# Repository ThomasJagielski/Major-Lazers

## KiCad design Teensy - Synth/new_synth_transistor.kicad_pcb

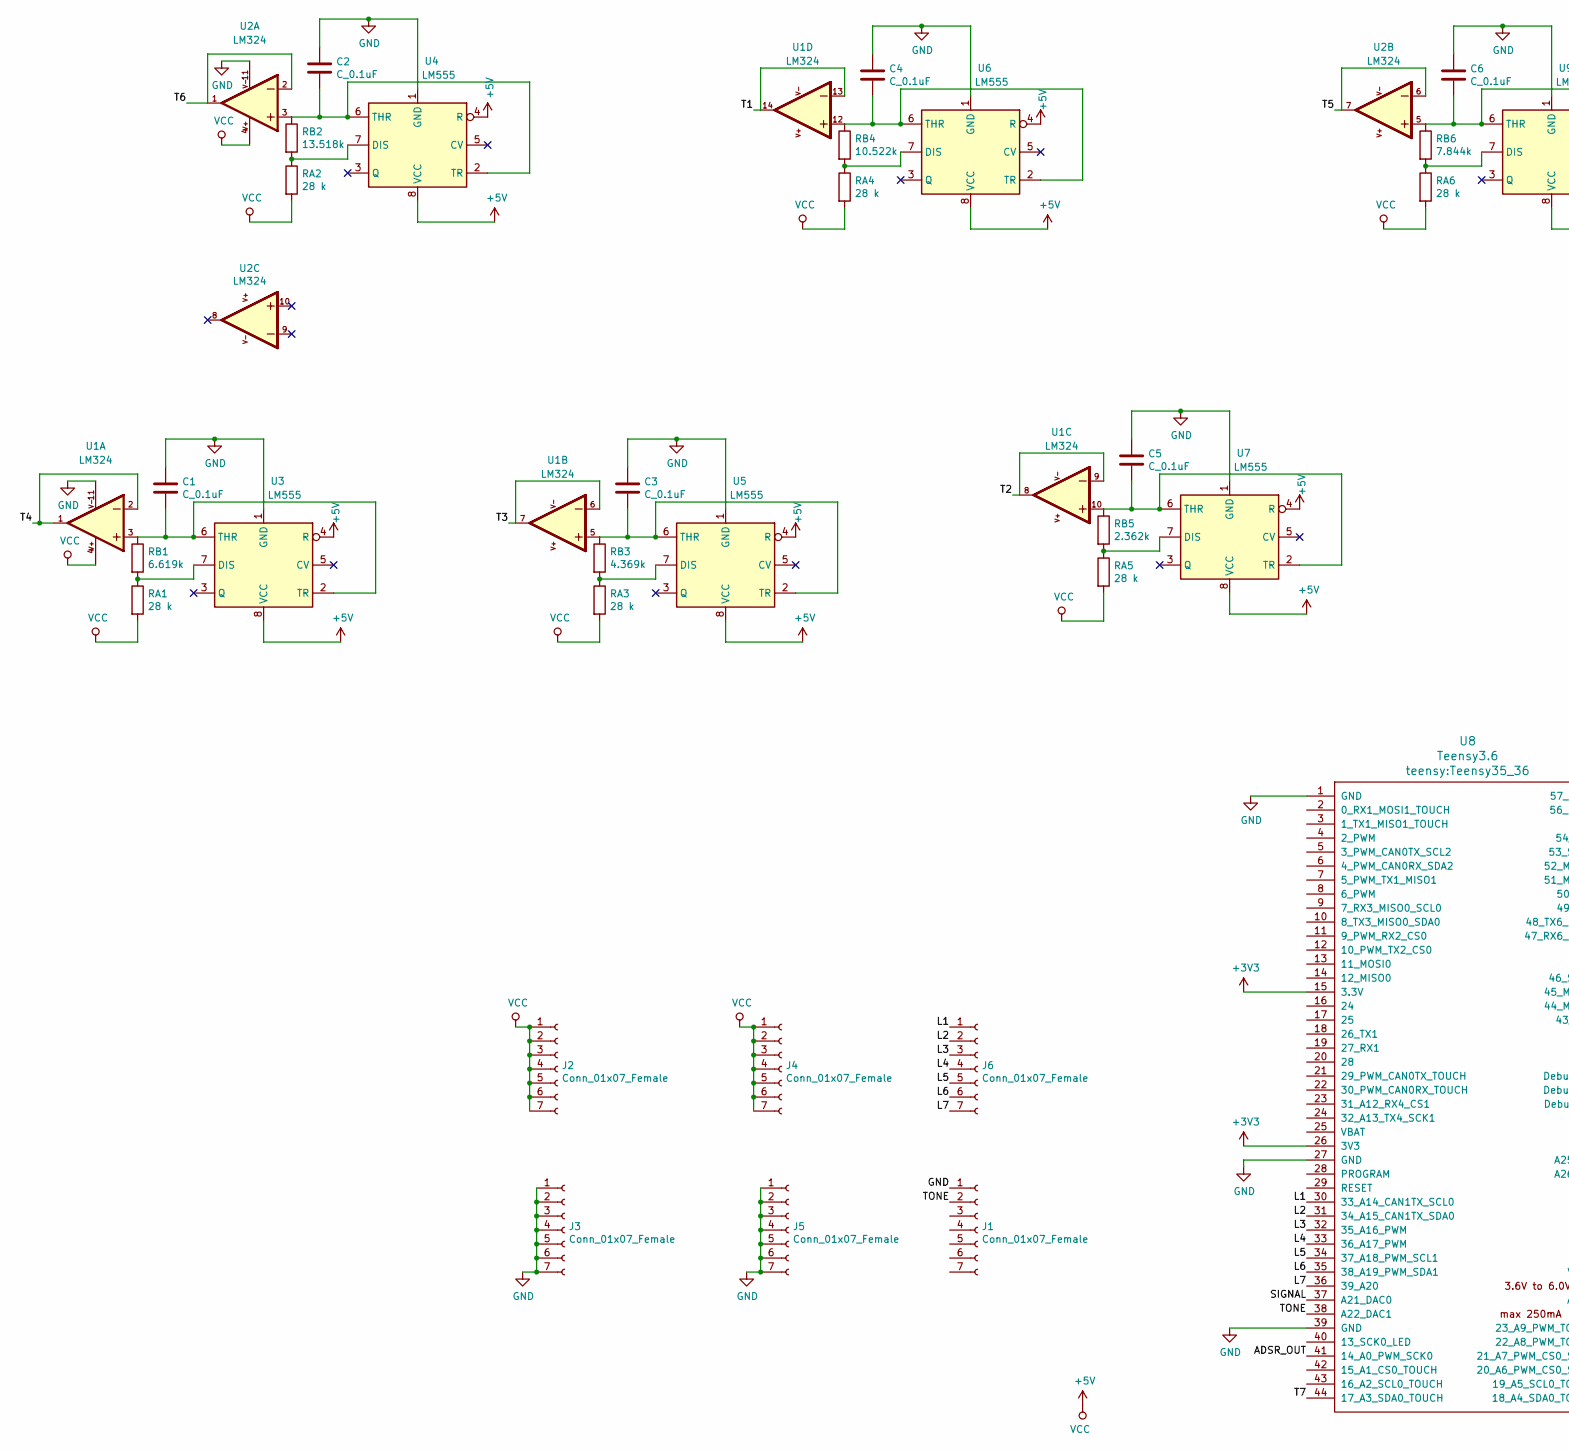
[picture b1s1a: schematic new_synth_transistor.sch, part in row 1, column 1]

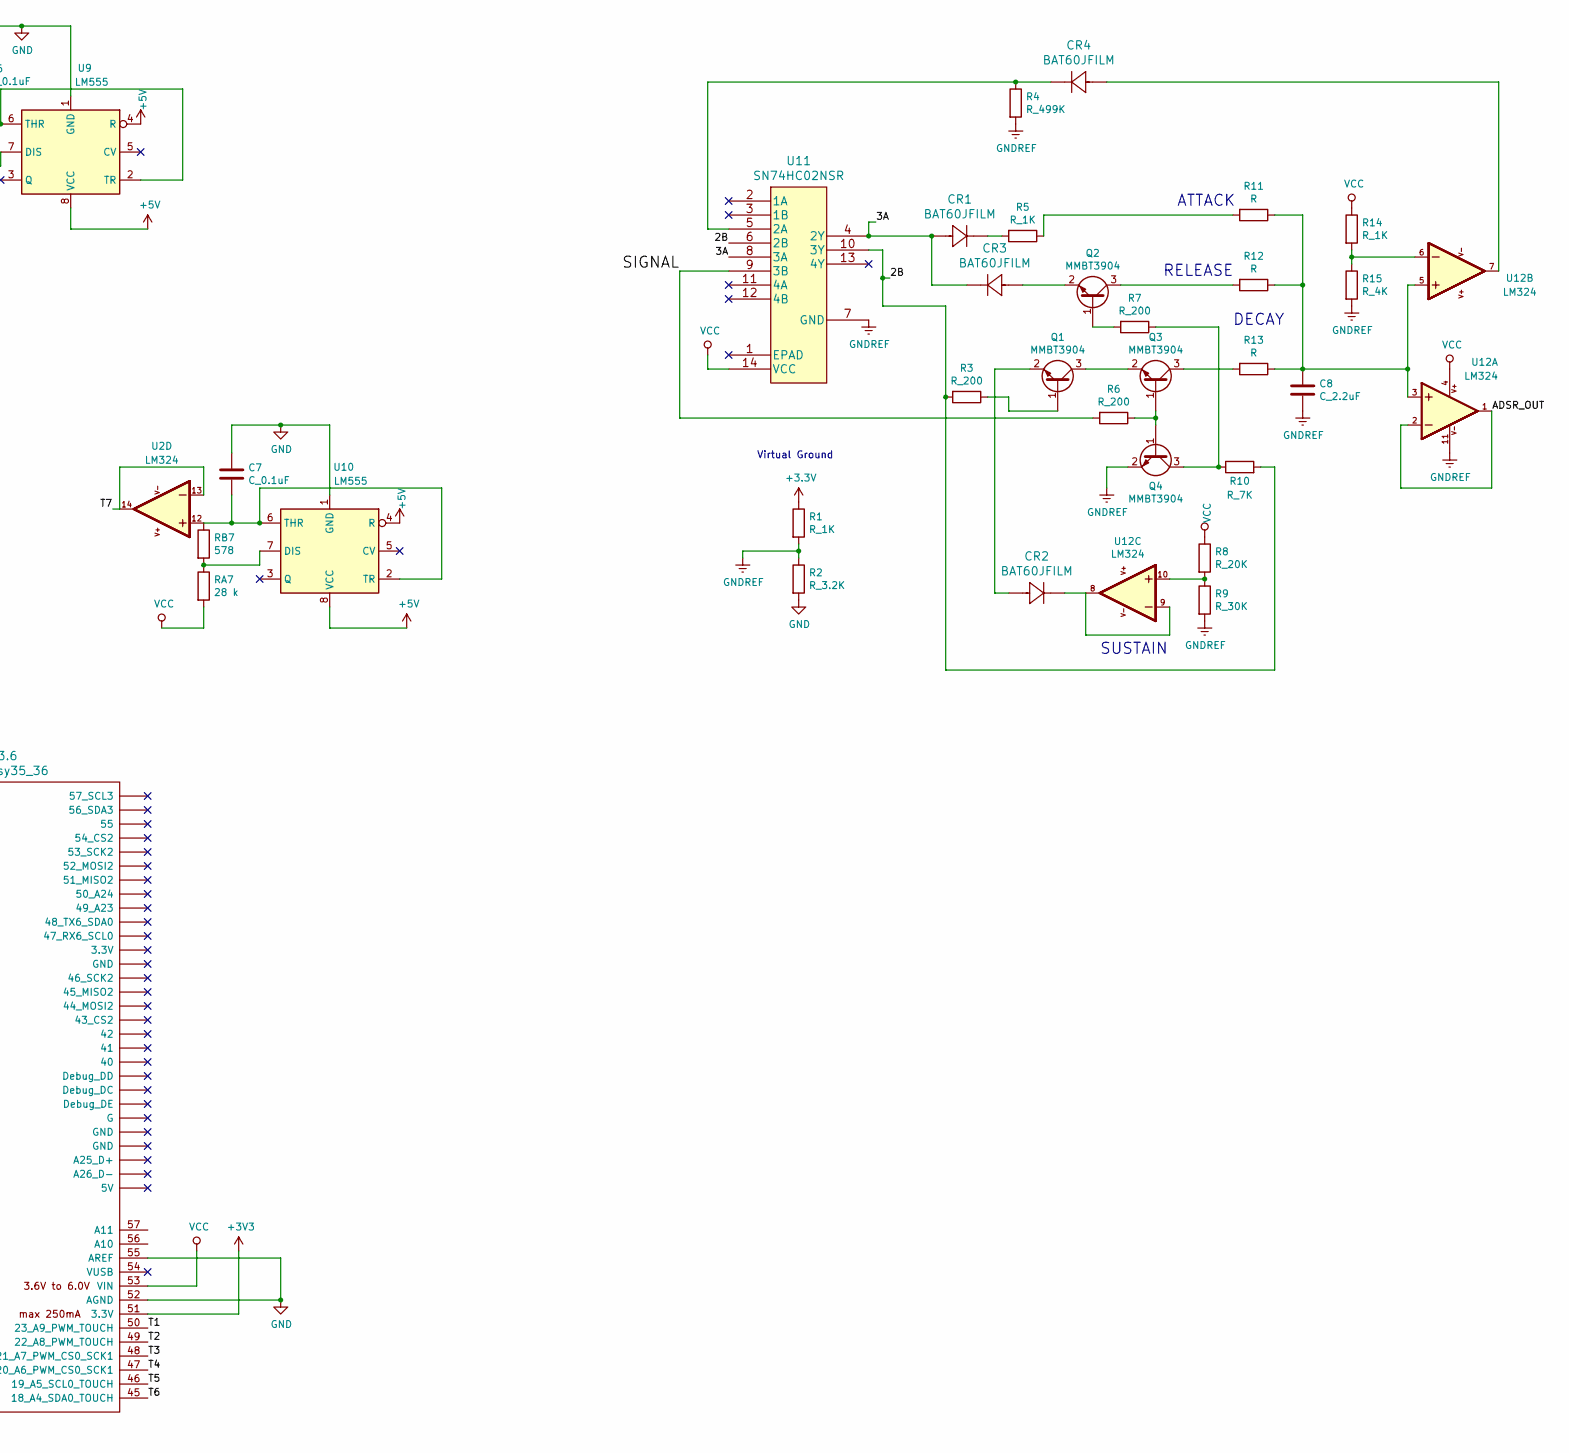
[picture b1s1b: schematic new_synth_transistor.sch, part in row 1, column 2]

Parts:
C1, C2, C3, C4, C5, C6, C7: C_0.1uF; C_0805_2012Metric
C8: C_2.2uF; C_0805_2012Metric
CR1, CR2, CR3, CR4: BAT60JFILM
J1, J2, J3, J4, J5, J6: Conn_01x07_Female; PinHeader_1x07_P2.54mm_Vertical
Q1, Q2, Q3, Q4: MMBT3904; SOT-23
R1, R5, R14: R_1K; R_0805_2012Metric
R2: R_3.2K; R_0805_2012Metric
R3, R6, R7: R_200; R_0805_2012Metric
R4: R_499K; R_0805_2012Metric
R8: R_20K; R_0805_2012Metric
R9: R_30K; R_0805_2012Metric
R10: R_7K; R_0805_2012Metric
R11, R12, R13: R; R_0805_2012Metric
R15: R_4K; R_0805_2012Metric
RA1, RA2, RA3, RA4, RA5, RA6, RA7: 28 k; R_0805_2012Metric
RB1: 6.619k; R_0805_2012Metric
RB2: 13.518k; R_0805_2012Metric
RB3: 4.369k; R_0805_2012Metric
RB4: 10.522k; R_0805_2012Metric
RB5: 2.362k; R_0805_2012Metric
RB6: 7.844k; R_0805_2012Metric
RB7: 578; R_0805_2012Metric
U1, U2, U12: LM324; SOIC127P600X175-14N
U3, U4, U5, U6, U7, U9, U10: LM555; SO08
U8: Teensy3.6; Teensy35_36
U11: SN74HC02NSR

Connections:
+5V: J2.1, J2.2, J2.3, J2.4, J2.5, J2.6, J2.7, J4.1, J4.2, J4.3, J4.4, J4.5, J4.6, J4.7, R8.1, R14.1, RA1.2, RA2.2, RA3.2, RA4.2, RA5.2, RA6.2, RA7.2, U1.4 (VCC+), U2.4 (VCC+), U3.4 (R), U3.8 (VCC), U4.4 (R), U4.8 (VCC), U5.4 (R), U5.8 (VCC), U6.4 (R), U6.8 (VCC), U7.4 (R), U7.8 (VCC), U8.53 (VIN), U9.4 (R), U9.8 (VCC), U10.4 (R), U10.8 (VCC), U11.14 (VCC), U12.4 (VCC+)
/2B: R3.2, R10.2, U11.6 (2B), U11.10 (3Y)
/3A: CR1.2, CR3.1, U11.4 (2Y), U11.8 (3A)
/ADSR_OUT: U8.41 (14_A0_PWM_SCK0), U12.1 (OUTPUT1), U12.2 (INVERTING_INPUT1)
/L1: J6.1, U8.30 (33_A14_CAN1TX_SCL0)
/L2: J6.2, U8.31 (34_A15_CAN1TX_SDA0)
/L3: J6.3, U8.32 (35_A16_PWM)
/L4: J6.4, U8.33 (36_A17_PWM)
/L5: J6.5, U8.34 (37_A18_PWM_SCL1)
/L6: J6.6, U8.35 (38_A19_PWM_SDA1)
/L7: J6.7, U8.36 (39_A20)
/SIGNAL: R6.2, U8.37 (A21_DAC0), U11.9 (3B)
/T1: U1.13 (INVERTING_INPUT4), U1.14 (OUTPUT4), U8.50 (23_A9_PWM_TOUCH)
/T2: U1.8 (OUTPUT3), U1.9 (INVERTING_INPUT3), U8.49 (22_A8_PWM_TOUCH)
/T3: U1.6 (INVERTING_INPUT2), U1.7 (OUTPUT2), U8.48 (21_A7_PWM_CS0_SCK1)
/T4: U1.1 (OUTPUT1), U1.2 (INVERTING_INPUT1), U8.47 (20_A6_PWM_CS0_SCK1)
/T5: U2.6 (INVERTING_INPUT2), U2.7 (OUTPUT2), U8.46 (19_A5_SCL0_TOUCH)
/T6: U2.1 (OUTPUT1), U2.2 (INVERTING_INPUT1), U8.45 (18_A4_SDA0_TOUCH)
/T7: U2.13 (INVERTING_INPUT4), U2.14 (OUTPUT4), U8.44 (17_A3_SDA0_TOUCH)
/TONE: J1.2, U8.38 (A22_DAC1)
GND: C1.1, C2.1, C3.1, C4.1, C5.1, C6.1, C7.1, J1.1, J3.1, J3.2, J3.3, J3.4, J3.5, J3.6, J3.7, J5.1, J5.2, J5.3, J5.4, J5.5, J5.6, J5.7, R2.2, U1.11 (VCC-), U2.11 (VCC-), U3.1 (GND), U4.1 (GND), U5.1 (GND), U6.1 (GND), U7.1 (GND), U8.1 (GND), U8.27 (GND), U8.39 (GND), U8.52 (AGND), U8.55 (AREF), U9.1 (GND), U10.1 (GND)
GNDREF: C8.2, Q4.2 (E), R1.2, R2.1, R4.2, R9.2, R15.2, U11.7 (GND), U12.11 (VCC-)
unnamed: C1.2, RB1.1, U1.3 (NON-INVERTING_INPUT1), U3.2 (TR), U3.6 (THR)
unnamed: C2.2, RB2.1, U2.3 (NON-INVERTING_INPUT1), U4.2 (TR), U4.6 (THR)
unnamed: C3.2, RB3.1, U1.5 (NON-INVERTING_INPUT2), U5.2 (TR), U5.6 (THR)
unnamed: C4.2, RB4.1, U1.12 (NON-INVERTING_INPUT4), U6.2 (TR), U6.6 (THR)
unnamed: C5.2, RB5.1, U1.10 (NON-INVERTING_INPUT3), U7.2 (TR), U7.6 (THR)
unnamed: C6.2, RB6.1, U2.5 (NON-INVERTING_INPUT2), U9.2 (TR), U9.6 (THR)
unnamed: C7.2, RB7.1, U2.12 (NON-INVERTING_INPUT4), U10.2 (TR), U10.6 (THR)
unnamed: C8.1, R11.1, R12.1, R13.1, U12.3 (NON-INVERTING_INPUT1), U12.5 (NON-INVERTING_INPUT2)
unnamed: CR1.1, R5.2
unnamed: CR2.1, U12.8 (OUTPUT3), U12.9 (INVERTING_INPUT3)
unnamed: CR2.2, Q1.2 (E)
unnamed: CR3.2, Q2.2 (E)
unnamed: CR4.1, R4.1, U11.5 (2A)
unnamed: CR4.2, U12.7 (OUTPUT2)
unnamed: Q1.1 (B), R3.1
unnamed: Q1.3 (C), Q3.2 (E)
unnamed: Q2.1 (B), R7.2
unnamed: Q2.3 (C), R12.2
unnamed: Q3.1 (B), Q4.1 (B), R6.1
unnamed: Q3.3 (C), R13.2
unnamed: Q4.3 (C), R7.1, R10.1
unnamed: R8.2, R9.1, U12.10 (NON-INVERTING_INPUT3)
unnamed: R5.1, R11.2
unnamed: R14.2, R15.1, U12.6 (INVERTING_INPUT2)
unnamed: RA1.1, RB1.2, U3.7 (DIS)
unnamed: RA2.1, RB2.2, U4.7 (DIS)
unnamed: RA3.1, RB3.2, U5.7 (DIS)
unnamed: RA4.1, RB4.2, U6.7 (DIS)
unnamed: RA5.1, RB5.2, U7.7 (DIS)
unnamed: RA6.1, RB6.2, U9.7 (DIS)
unnamed: RA7.1, RB7.2, U10.7 (DIS)

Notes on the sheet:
SUSTAIN
DECAY
ATTACK
RELEASE
Virtual Ground

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
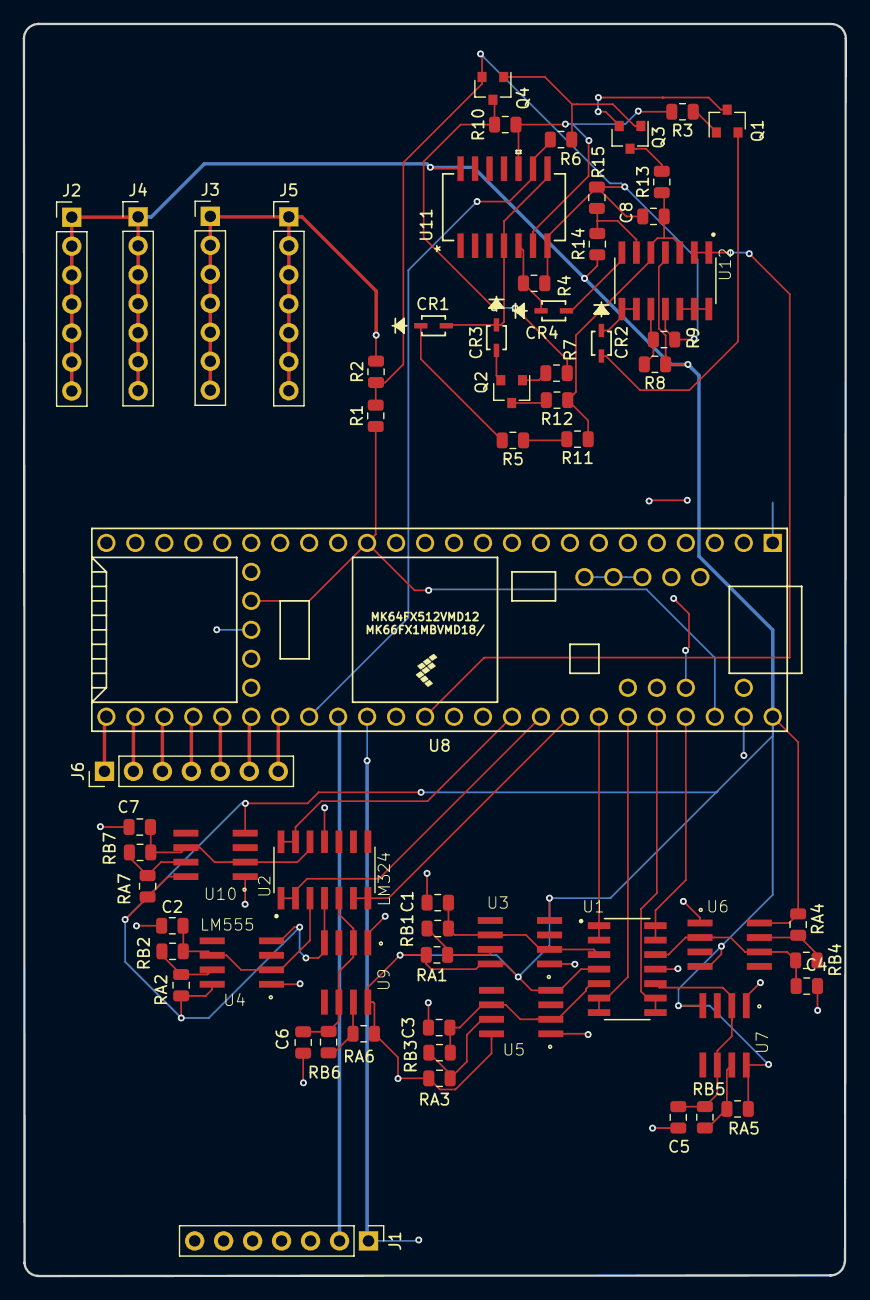
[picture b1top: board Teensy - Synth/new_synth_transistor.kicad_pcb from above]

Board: 2 copper layers, 72.1 x 109.8 mm, 63 parts (0 on the bottom side), 54 nets.

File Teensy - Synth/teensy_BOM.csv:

"Id";"Designator";"Package";"Quantity";"Designation";"Supplier and ref";
1;"U12,U1,U2";"SOIC127P600X175-14N";3;"LM324";;;
2;"U10,U6,U4,U3,U5,U7,U9";"SO08";7;"LM555";;;
3;"U11";"SN74HC02NSR";1;"SN74HC02NSR";;;
4;"U8";"Teensy35_36";1;"Teensy3.6";;;
5;"C1,C2,C3,C4,C5,C6,C7";"C_0805_2012Metric";7;"C_0.1uF";;;
6;"C8";"C_0805_2012Metric";1;"C_2.2uF";;;
7;"CR1,CR2,CR3,CR4";"BAT60JFILM";4;"BAT60JFILM";;;
8;"J1,J2,J3,J4,J5,J6";"PinHeader_1x07_P2.54mm_Vertical";6;"Conn_01x07_Female";;;
9;"Q1,Q2,Q3,Q4";"SOT-23";4;"MMBT3904";;;
10;"R1,R5,R14";"R_0805_2012Metric";3;"R_1K";;;
11;"R2";"R_0805_2012Metric";1;"R_3.2K";;;
12;"R3,R6,R7";"R_0805_2012Metric";3;"R_200";;;
13;"R4";"R_0805_2012Metric";1;"R_499K";;;
14;"R8";"R_0805_2012Metric";1;"R_20K";;;
15;"R9";"R_0805_2012Metric";1;"R_30K";;;
16;"R10";"R_0805_2012Metric";1;"R_7K";;;
17;"R11,R12,R13";"R_0805_2012Metric";3;"R";;;
18;"R15";"R_0805_2012Metric";1;"R_4K";;;
19;"RA1,RA2,RA3,RA4,RA5,RA6,RA7";"R_0805_2012Metric";7;"28 k";;;
20;"RB1";"R_0805_2012Metric";1;"6.619k";;;
21;"RB2";"R_0805_2012Metric";1;"13.518k";;;
22;"RB3";"R_0805_2012Metric";1;"4.369k";;;
23;"RB4";"R_0805_2012Metric";1;"10.522k";;;
24;"RB5";"R_0805_2012Metric";1;"2.362k";;;
25;"RB6";"R_0805_2012Metric";1;"7.844k";;;
26;"RB7";"R_0805_2012Metric";1;"578";;;

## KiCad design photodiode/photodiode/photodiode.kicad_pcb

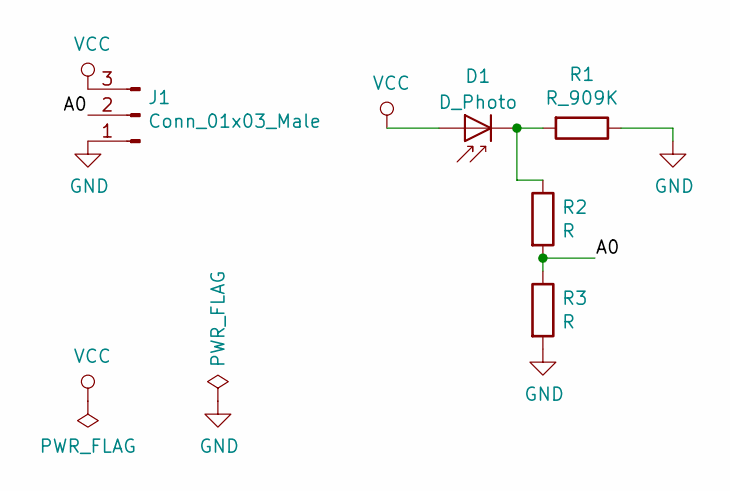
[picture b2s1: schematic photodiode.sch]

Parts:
D1: D_Photo; PinHeader_1x02_P2.54mm_Vertical
J1: Conn_01x03_Male; PinHeader_1x03_P2.54mm_Vertical
R1: R_909K; R_0805_2012Metric
R2, R3: R; R_0805_2012Metric

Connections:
/A0: J1.2, R2.2, R3.1
GND: J1.1, R1.1, R3.2
unnamed: D1.1 (K), R1.2, R2.1
VCC: D1.2 (A), J1.3

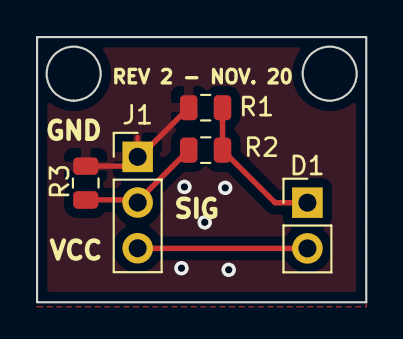
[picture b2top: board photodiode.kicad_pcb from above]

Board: 2 copper layers, 18.3 x 14.7 mm, 5 parts (0 on the bottom side), 4 nets.

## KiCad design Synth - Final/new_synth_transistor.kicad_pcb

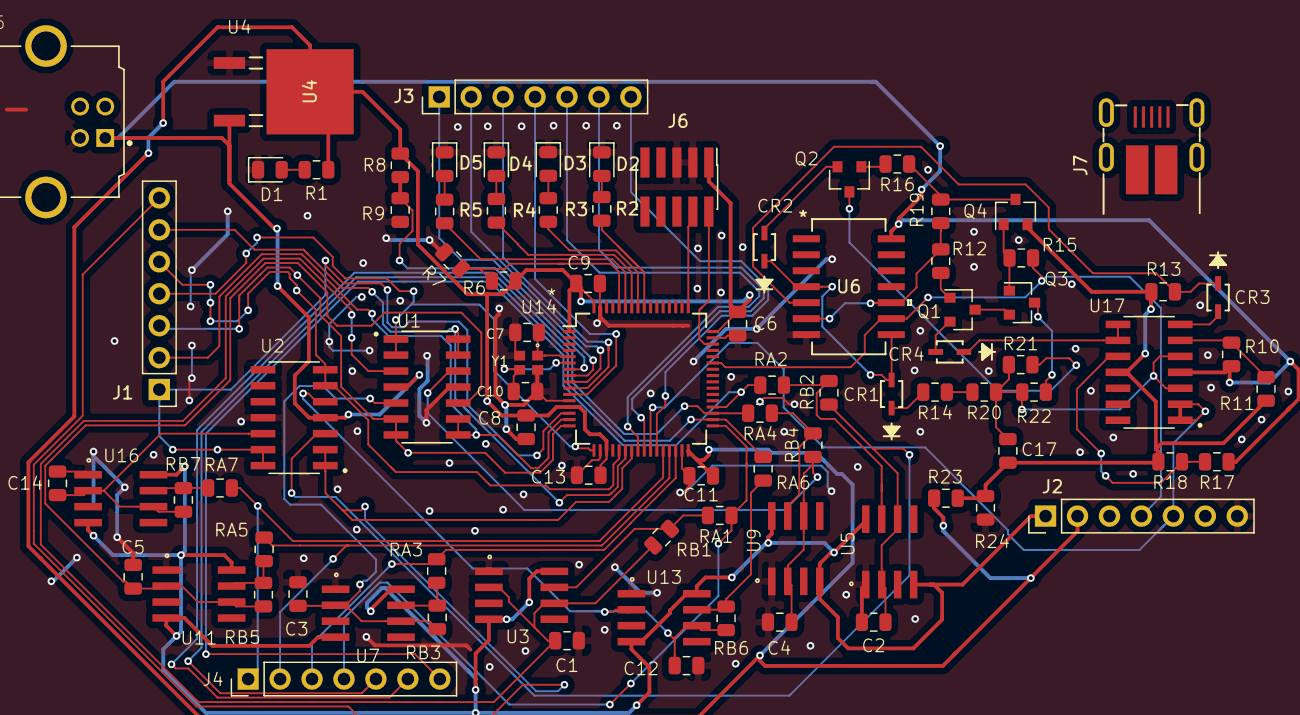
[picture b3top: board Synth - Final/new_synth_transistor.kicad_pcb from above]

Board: 2 copper layers, 87 parts (0 on the bottom side), 76 nets.

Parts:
C1, C2, C3, C4, C5, C6, C8, C9, C11, C12, C13, C14: C_0.1uF; C_0805_2012Metric
C7, C10: C_22pF; C_0805_2012Metric
C17: C_2.2uF; C_0805_2012Metric
CR1, CR2, CR3, CR4: BAT60JFILM
D1, D2, D3, D4, D5: LED; D_0805_2012Metric
J1, J2, J3, J4: Conn_01x07_Male; PinHeader_1x07_P2.54mm_Vertical
J5: USB_B; ASSMANN_AU-Y1007
J6: Conn_ARM_JTAG_SWD_10; PinHeader_2x05_P1.27mm_Vertical_SMD
J7: UJ2-MIBH-4-SMT-TR; USB_Micro_B_Male_UJ2-MIBH-4-SMT-TR
Q1, Q2, Q3, Q4: MMBT3904; SOT-23
R1, R2, R3, R4, R5, R12, R15, R16: R_200; R_0805_2012Metric
R6, R7, R8, R9: R_0; R_0805_2012Metric
R10, R14, R23: R_1K; R_0805_2012Metric
R11: R_4K; R_0805_2012Metric
R13: R_499K; R_0805_2012Metric
R17: R_20K; R_0805_2012Metric
R18: R_30K; R_0805_2012Metric
R19: R_7K; R_0805_2012Metric
R20, R21, R22: R; R_0805_2012Metric
R24: R_3.2K; R_0805_2012Metric
RA1, RA2, RA3, RA4, RA5, RA6, RA7: 28 k; R_0805_2012Metric
RB1: 6.619k; R_0805_2012Metric
RB2: 13.518k; R_0805_2012Metric
RB3: 4.369k; R_0805_2012Metric
RB4: 10.522k; R_0805_2012Metric
RB5: 2.362k; R_0805_2012Metric
RB6: 7.844k; R_0805_2012Metric
RB7: 578; R_0805_2012Metric
U1, U2, U17: LM324; SOIC127P600X175-14N
U3, U5, U7, U9, U11, U13, U16: LM555; SO08
U4: U4; NCP1117DT33T5G
U6: SN74HC02NSR
U14: STM32F072RBTx; LQFP-64_10x10mm_P0.5mm
Y1: Crystal_32MHz; OSCCC200X160X50N

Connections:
+3V3: C6.1, C8.1, C9.1, C11.1, C13.1, J2.2, J6.1, R1.1, R6.1, R8.1, R23.1, U4.2, U14.1, U14.13, U14.19, U14.32, U14.48, U14.64
+5V: J2.1, U3.4, U3.8, U5.4, U5.8, U7.4, U7.8, U9.4, U9.8, U11.4, U11.8, U13.4, U13.8, U16.4, U16.8
/2B: R12.2, R19.2, U6.6, U6.10
/3A: CR1.2, CR2.1, U6.4, U6.8
/ADSR_OUT: J2.5, U14.26, U17.1, U17.2
/D7: J4.1, RA7.2, U14.28
/D8: J4.2, RA5.2, U14.29
/D9: J4.3, RA3.2, U14.30
/D10: J4.4, RA1.2, U14.33
/D11: J4.5, RA6.2, U14.34
/D12: J4.6, RA4.2, U14.35
/D13: J4.7, RA2.2, U14.36
/L1: J3.1, U14.8
/L2: J3.2, U14.9
/L3: J3.3, U14.10
/L4: J3.4, U14.11
/L5: J3.5, U14.24
/L6: J3.6, U14.25
/L7: J3.7, U14.27
/LED1: R2.1, U14.56
/LED2: R3.1, U14.57
/LED3: R4.1, U14.58
/LED4: R5.1, U14.59
/SIGNAL: J2.4, R15.2, U6.9, U14.43
/SWCLK: J6.4, U14.49
/SWDIO: J6.2, U14.46
/T7: J1.1, U2.13, U2.14, U14.14
/T8: J1.2, U1.8, U1.9, U14.15
/T9: J1.3, U1.6, U1.7, U14.16
/T10: J1.4, U1.1, U1.2, U14.17
/T11: J1.5, U2.6, U2.7, U14.21
/T12: J1.6, U1.13, U1.14, U14.22
/T13: J1.7, U2.1, U2.2, U14.23
GND: C1.1, C2.1, C3.1, C4.1, C5.1, C6.2, C7.2, C8.2, C9.2, C10.2, C11.2, C12.1, C13.2, C14.1, D1.1, D2.1, D3.1, D4.1, D5.1, J2.7, J5.4, J6.3, J6.5, R7.2, R9.2, R24.2, U1.11, U2.11, U3.1, U4.1, U5.1, U6.7, U7.1, U9.1, U11.1, U13.1, U14.12, U14.18, U14.31, U14.47, U14.63, U16.1, Y1.2, Y1.4
GNDREF: C17.2, Q4.2, R11.2, R13.2, R18.2, R23.2, R24.1, U17.11
unnamed: C1.2, RB1.1, U1.3, U3.2, U3.6
unnamed: C2.2, RB2.1, U2.3, U5.2, U5.6
unnamed: C3.2, RB3.1, U1.5, U7.2, U7.6
unnamed: C4.2, RB4.1, U1.12, U9.2, U9.6
unnamed: C5.2, RB5.1, U1.10, U11.2, U11.6
unnamed: C7.1, U14.5, Y1.1
unnamed: C10.1, U14.6, Y1.3
unnamed: C12.2, RB6.1, U2.5, U13.2, U13.6
unnamed: C14.2, RB7.1, U2.12, U16.2, U16.6
unnamed: C17.1, R20.1, R21.1, R22.1, U17.3, U17.5
unnamed: CR1.1, R14.2
unnamed: CR2.2, Q2.2
unnamed: CR3.1, R13.1, U6.5
unnamed: CR3.2, U17.7
unnamed: CR4.1, U17.8, U17.9
unnamed: CR4.2, Q1.2
unnamed: D1.2, R1.2
unnamed: D2.2, R2.2
unnamed: D3.2, R3.2
unnamed: D4.2, R4.2
unnamed: D5.2, R5.2
unnamed: Q1.1, R12.1
unnamed: Q1.3, Q3.2
unnamed: Q2.1, R16.2
unnamed: Q2.3, R21.2
unnamed: Q3.1, Q4.1, R15.1
unnamed: Q3.3, R22.2
unnamed: Q4.3, R16.1, R19.1
unnamed: R6.2, R7.1, U14.60
unnamed: R8.2, R9.1, U14.7
unnamed: R10.2, R11.1, U17.6
unnamed: R14.1, R20.2
unnamed: R17.2, R18.1, U17.10
unnamed: RA1.1, RB1.2, U3.7
unnamed: RA2.1, RB2.2, U5.7
unnamed: RA3.1, RB3.2, U7.7
unnamed: RA4.1, RB4.2, U9.7
unnamed: RA5.1, RB5.2, U11.7
unnamed: RA6.1, RB6.2, U13.7
unnamed: RA7.1, RB7.2, U16.7
VCC: J5.1, R10.1, R17.1, U1.4, U2.4, U4.3, U6.14, U17.4

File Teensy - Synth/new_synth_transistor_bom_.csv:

Component,Description,Part,References,Value,Footprint,Quantity Per PCB,Datasheet,Field8,Field4,Field7,Field6,Field5
1,Unpolarized capacitor,C,C1 C2 C3 C4 C5 C6 C8 C9 C11 C12 C13 C14,C_0.1uF,C_0805_2012Metric,12,~,,,,,
2,Unpolarized capacitor,C,C17,C_2.2uF,C_0805_2012Metric,1,~,,,,,
3,Unpolarized capacitor,C,C7 C10,C_22pF,C_0805_2012Metric,2,~,,,,,
4,,BAT60JFILM,CR1 CR2 CR3 CR4,BAT60JFILM,BAT60JFILM,4,,,,,,
5,Light emitting diode,LED,D1 D2 D3 D4 D5,LED,D_0805_2012Metric,5,~,,,,,
6,"Generic connector, single row, 01x02, script generated (kicad-library-utils/schlib/autogen/connector/)",Conn_01x02_Male,J8,Conn_01x02_Male,PinHeader_1x02_P2.54mm_Vertical,1,~,,,,,
7,"Generic connector, single row, 01x07, script generated (kicad-library-utils/schlib/autogen/connector/)",Conn_01x07_Male,J1 J2 J3 J4,Conn_01x07_Male,PinHeader_1x07_P2.54mm_Vertical,4,~,,,,,
8,"Cortex Debug Connector, standard ARM Cortex-M SWD and JTAG interface",Conn_ARM_JTAG_SWD_10,J6,Conn_ARM_JTAG_SWD_10,PinHeader_2x05_P1.27mm_Vertical_SMD,1,http://infocenter.arm.com/help/topic/com.arm.doc.faqs/attach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,,,,,
9,USB Type B connector,USB_B,J5 J7,USB_B,ASSMANN_AU-Y1007,2, ~,,,,,
10,"0.2A Ic, 40V Vce, Small Signal NPN Transistor, SOT-23",MMBT3904,Q1 Q2 Q3 Q4,MMBT3904,SOT-23,4,https://www.fairchildsemi.com/datasheets/2N/2N3904.pdf,,,,,
11,Resistor,R,R20 R21 R22,R,R_0805_2012Metric,3,~,,,,,
12,Resistor,R,R6 R7 R8 R9,R_0,R_0805_2012Metric,4,~,,,,,
13,Resistor,R,R10 R14 R23,R_1K,R_0805_2012Metric,3,~,,,,,
14,Resistor,R,R1 R2 R3 R4 R5 R12 R15 R16,R_200,R_0805_2012Metric,8,~,,,,,
15,Resistor,R,R17,R_20K,R_0805_2012Metric,1,~,,,,,
16,Resistor,R,R24,R_3.2K,R_0805_2012Metric,1,~,,,,,
17,Resistor,R,R18,R_30K,R_0805_2012Metric,1,~,,,,,
18,Resistor,R,R13,R_499K,R_0805_2012Metric,1,~,,,,,
19,Resistor,R,R11,R_4K,R_0805_2012Metric,1,~,,,,,
20,Resistor,R,R19,R_7K,R_0805_2012Metric,1,~,,,,,
21,Resistor,R,RA1 RA2 RA3 RA4 RA5 RA6 RA7,28 k,R_0805_2012Metric,7,~,,,,,
22,Resistor,R,RB4,10.522k,R_0805_2012Metric,1,~,,,,,
23,Resistor,R,RB2,13.518k,R_0805_2012Metric,1,~,,,,,
24,Resistor,R,RB5,2.362k,R_0805_2012Metric,1,~,,,,,
25,Resistor,R,RB3,4.369k,R_0805_2012Metric,1,~,,,,,
26,Resistor,R,RB7,578,R_0805_2012Metric,1,~,,,,,
27,Resistor,R,RB1,6.619k,R_0805_2012Metric,1,~,,,,,
28,Resistor,R,RB6,7.844k,R_0805_2012Metric,1,~,,,,,
29,,LM324,U1 U2 U17,LM324,SOIC127P600X175-14N,3,these devices consist of four independent high-gain frequency-compensated operational amplifiers that are designed sp...,SOIC-14 Texas Instruments,Texas Instruments,LM324,None,Unavailable
30,"Timer, DIP-8/SOIC-8/SSOP-8",LM555,U3 U5 U7 U9 U11 U13 U16,LM555,SO08,7,http://www.ti.com/lit/ds/symlink/lm555.pdf,,,,,
31,,NCP1117DT33T5G,U4,NCP1117DT33T5G,NCP1117DT33T5G,1,,,,,,
32,,SN74HC02NSR,U6,SN74HC02NSR,SN74HC02NSR,1,,,,,,
33,"ARM Cortex-M0 MCU, 128KB flash, 16KB RAM, 48MHz, 2-3.6V, 51 GPIO, LQFP-64",STM32F072RBTx,U14,STM32F072RBTx,LQFP-64_10x10mm_P0.5mm,1,http://www.st.com/st-web-ui/static/active/en/resource/techni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,,,,,
34,"Four pin crystal, GND on pins 2 and 4",Crystal_GND24,Y1,Crystal_32MHz,OSCCC200X160X50N,1,~,,,,,





Component Groups:,34
Component Count:,88
Fitted Components:,88
Number of PCBs:,1
Total components:,88
Schematic Version:,
Schematic Date:,
PCB Variant:,default
BoM Date:,11/12/2019 10:54:52 AM
Schematic Source:,C:\Users\tjagielski\Documents\Projects\School\Sophomore - Semester 1\POE\Final Project\Major-Lazers\Synth - Final\new_synth_transistor.sch
KiCad Version:,Eeschema (5.0.1)-4

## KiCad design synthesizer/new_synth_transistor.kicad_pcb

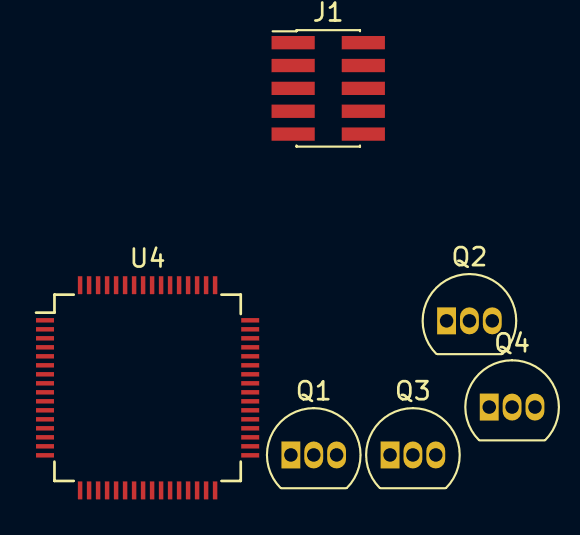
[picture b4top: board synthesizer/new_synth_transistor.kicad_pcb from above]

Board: 2 copper layers, 6 parts (0 on the bottom side), 4 nets, no tracks yet.

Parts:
J1: Conn_ARM_JTAG_SWD_10; PinHeader_2x05_P1.27mm_Vertical_SMD
Q1, Q2, Q3, Q4: 2N3904; TO-92_Inline
U4: STM32F072RBTx; LQFP-64_10x10mm_P0.5mm

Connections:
unnamed: J1.3, J1.5
unnamed: Q1.3, Q3.1
unnamed: Q2.2, Q4.3
unnamed: Q3.2, Q4.2

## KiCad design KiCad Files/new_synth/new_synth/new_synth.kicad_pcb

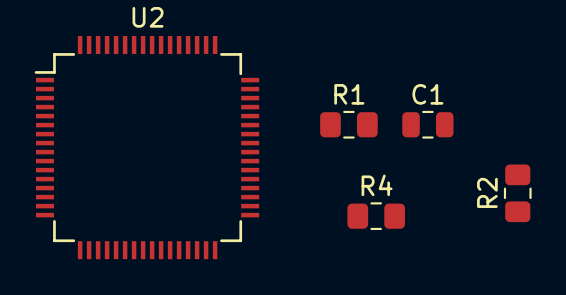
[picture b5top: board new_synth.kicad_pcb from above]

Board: 2 copper layers, 5 parts (0 on the bottom side), 2 nets, no tracks yet.

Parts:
C1: C; C_0805_2012Metric
R1, R2, R4: R; R_0805_2012Metric_Pad1.15x1.40mm_HandSolder
U2: STM32F072RBTx; LQFP-64_10x10mm_P0.5mm

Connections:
GND: C1.2, R2.2
unnamed: C1.1, R1.2

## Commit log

2019-10-21 Created README
2019-10-21 init website
2019-10-21 laser led test
2019-10-22 Testing speaker
    Using arduino tone library connected to stripped aux cable to speaker
2019-10-22 Update Speaker_Note.ino
    Added comment
2019-10-23 home template and style css
2019-10-24 laser to sound; speaker integration
2019-10-31 first rev schematic
2019-11-05 Adding new synth with transistors as switches
2019-11-05 Update STM32 Chip
2019-11-06 Final Schematic
2019-11-08 Update lasernotetest.ino
    Values adjusted
2019-11-10 Add PCB
2019-11-11 photodiode pcb
2019-11-11 Update pcb layout
2019-11-11 Add synth Gerber file
2019-11-11 adding pcb info
2019-11-11 updating photodiode pcb
2019-11-15 font for website
2019-11-18 Adding updates
2019-11-20 Teensy Test code
2019-11-20 Adding ADSR
2019-11-20 Rev 2 of photodiode PCB
2019-11-21 7 pins Teensy code
2019-11-21 Teensy code
2019-11-22 Sprint 3 code
2019-11-22 website, layout, and main, clean code
2019-11-24 Add Teensy Synth PCB
2019-11-25 blog structure
2019-11-25 do not pull, trying to fix kicad libraries
2019-11-25 Revert to Teesy PCB files
2019-11-26 Adding new paths for libraries, new component annotations, and netlist
2019-11-26 website gallery formatting and libraries and layout (almost done)
2019-11-27 Add voltage divider to photodiode circuit/pcb
2019-11-27 Add ZIP gerber files for photodiode to gerber folder
2019-11-27 final layout, no dxf
2019-11-27 Add ADSR Singal
2019-11-27 Add ADSR Signal
2019-11-27 dxf added to teensy pcb rev 2
2019-11-27 2 layers
2019-11-27 2 layers not 6 lol
2019-11-28 Updates to PCB
2019-11-29 gerbers
2019-11-29 Re-add KiCad files to revert changes
2019-11-29 if anything goes wrong go back to this
2019-11-29 Add REV 2 of synth of Gerbers folder
2019-11-29 PCB updates
2019-12-02 REV 3 of PCB
2019-12-03 photodiode gerber
2019-12-03 footer, team photo hover color
2019-12-03 led strip test
2019-12-03 Neopixels update
2019-12-05 Add new pcb
2019-12-06 website -> docs
2019-12-09 lots of website stuff: documentation images, process, subsystems, etc.
2019-12-09 website studd
2019-12-10 Add the ADSR code
2019-12-10 Final code
2019-12-10 Updating the Teensy code
2019-12-11 Fixing typo
2019-12-11 Updated concept
2019-12-12 new template
2019-12-12 home and process
2019-12-12 index w new theme
2019-12-12 first iteration of index/home
2019-12-12 nav bar and logo in process
2019-12-12 Update the process page
2019-12-12 subsystems template
2019-12-12 process header
2019-12-12 Updates to electrical page
2019-12-12 Update software page
2019-12-12 Adding Mechanical Page
2019-12-12 Add github link to all pages and fix logo
2019-12-12 Make updates to pages
2019-12-13 process, electrical done!
2019-12-13 Add budget to the process page
2019-12-13 Add final sprint content to the process page
2019-12-13 Add image
2019-12-13 four images on one row, process lines, overall, subsystems, blog templates
2019-12-13 First blog entry added
2019-12-13 Add photo to gallery
2019-12-13 Add blog posts
2019-12-13 Updated budget table
2019-12-13 Add weeekly blog entries
2019-12-13 Blogs almost done
2019-12-13 Got rid of old blog pages
2019-12-13 Updated team bios
2019-12-13 Team justify alignment added
2019-12-13 Justify aligned blogs
2019-12-13 mechanical page and images, team, subsystems!
2019-12-13 dhara bio
2019-12-13 mechanical image format

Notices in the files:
parts and their libraries:
Copyright 2016 Accelerated Designs. All rights reserved.
